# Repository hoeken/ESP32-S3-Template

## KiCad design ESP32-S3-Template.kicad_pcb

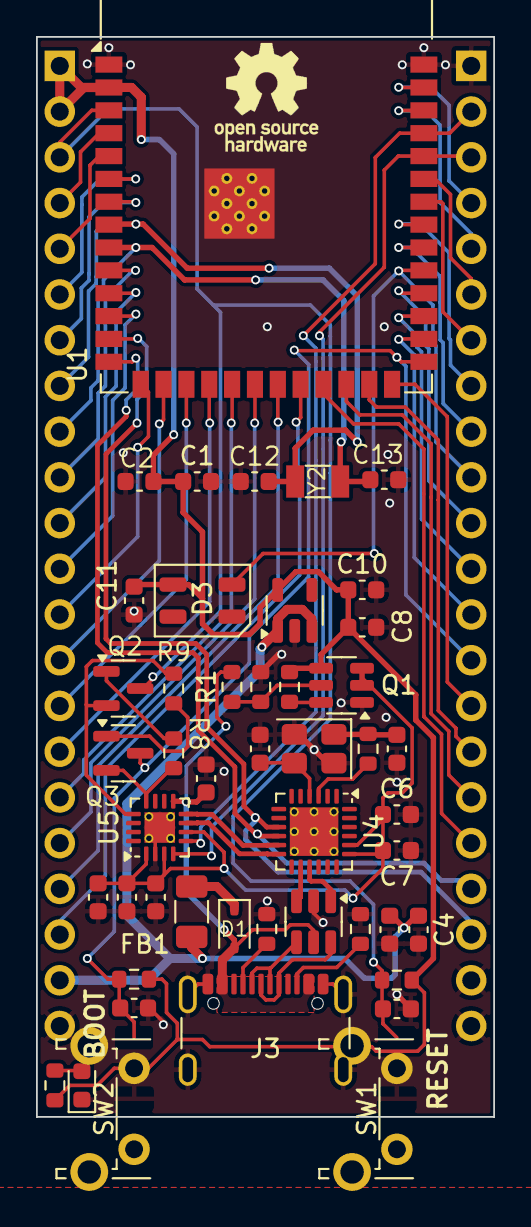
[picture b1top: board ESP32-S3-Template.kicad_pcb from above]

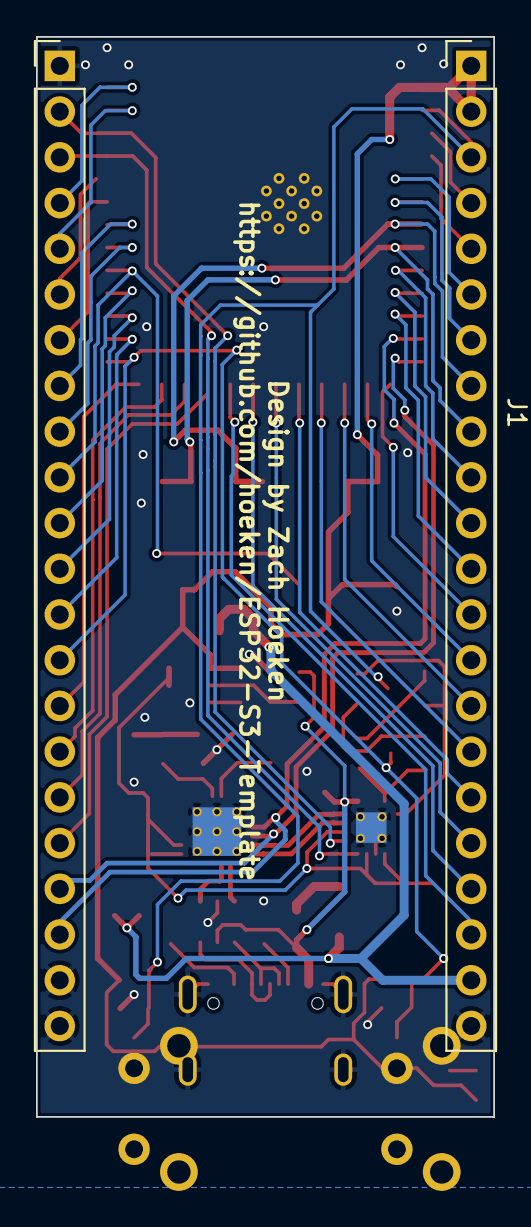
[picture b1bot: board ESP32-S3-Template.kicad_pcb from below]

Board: 4 copper layers, 25.4 x 60.0 mm, 50 parts (2 on the bottom side), 61 nets.

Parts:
C1: 22uF; C_0603_1608Metric
C2, C11, C14, C15, C17: 100nF; C_0603_1608Metric
C3, C10, C16: 10uF; C_0603_1608Metric
C4, C6, C7, C8, C19: 1uF; C_0603_1608Metric
C5, C9, C12, C13: 15pF; C_0603_1608Metric
C18: 4.7uF; C_0603_1608Metric
D1: 1N5819WS; D_SOD-323
D2: RED; LED_0603_1608Metric
D3: WS2812B-Mini; LED_WS2812B-Mini_PLCC4_3.5x3.5mm
FB1: 1.5A; Fuse_1206_3216Metric
J1, J2: Conn_01x22; PinHeader_1x22_P2.54mm_Vertical
J3: USB_TYPE_C_16PIN; USB_C_Receptacle_GCT_USB4105-xx-A_16P_TopMnt_Horizontal
Q1: FDC6330L; TSOT-23-6
Q2, Q3: S8050; SOT-23
R1: 100R; R_0603_1608Metric
R2, R3: 100k; R_0603_1608Metric
R4, R5, R6: 5.1k; R_0603_1608Metric
R7: 1k; R_0603_1608Metric
R8, R9, R10, R11: 10k; R_0603_1608Metric
S1: Logo_Open_Hardware_Small; OSHW-Logo_5.7x6mm_SilkScreen
SW1: RESET; SW_Tactile_SPST_Angled_PTS645Vx58-2LFS
SW2: BOOT; SW_Tactile_SPST_Angled_PTS645Vx58-2LFS
U1: ESP32-S3-WROOM-1-N16R8; ESP32-S3-WROOM-1
U2: USBLC6-2SC6; SOT-23-6
U3: XC6210B332MR; SOT-23-5
U4: CH334F; QFN-24-1EP_4x4mm_P0.5mm_EP2.7x2.7mm_ThermalVias
U5: CH343P; QFN-16-1EP_3x3mm_P0.5mm_EP1.7x1.7mm_ThermalVias
Y1: 12Mhz; Crystal_SMD_SeikoEpson_TSX3225-4Pin_3.2x2.5mm
Y2: 32.768kHz; Crystal_SMD_3215-2Pin_3.2x1.5mm

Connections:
+3.3V: C1.1, C2.1, C8.1, C10.1, C11.1, D2.2 (A), D3.1 (VDD), J1.1, J1.2, Q1.4 (S2), R2.2, R10.1, R11.2, U1.2 (3V3), U3.5 (VOUT)
+5V: C3.1, C4.1, FB1.2, J1.21, U3.1 (VIN), U3.3 (CE)
/ENABLE: C18.1, J1.3, Q2.3 (C), R10.2, SW1.1, U1.3 (EN)
/ESP32-S3/3.3VUSB: C6.1, C7.2, C14.1, C15.1, C17.1, Q1.2 (D2), Q1.3 (D2), U4.19 (V5), U4.20 (V33), U5.1 (VIO), U5.3 (VDD5), U5.6 (V3_{OUT})
/ESP32-S3/CC1_1: J3.A5 (CC1), R4.1
/ESP32-S3/CC2_1: J3.B5 (CC2), R5.1
/ESP32-S3/DTR: Q3.2 (E), R8.1, U5.12 (~DTR)
/ESP32-S3/HUB_D+: U2.1 (I/O1), U4.15 (D+U)
/ESP32-S3/HUB_D-: U2.3 (I/O2), U4.14 (D-U)
/ESP32-S3/RTS: Q2.2 (E), R9.1, U5.13 (~RTS)
/ESP32-S3/UART_D+: U4.12 (D+1), U5.7 (UD+)
/ESP32-S3/UART_D-: U4.11 (D-1), U5.8 (UD-)
/ESP32-S3/USB_D+: J3.A6 (D+), J3.B6 (D+), U2.6 (I/O1)
/ESP32-S3/USB_D-: J3.A7 (D-), J3.B7 (D-), U2.4 (I/O2)
/ESP32-S3/VBUS: C16.2, D1.2 (A), J3.A4 (VBUS), J3.A9 (VBUS), J3.B4 (VBUS), J3.B9 (VBUS), R1.2, U2.5 (VBUS), U5.9 (VBUS)
/ESP_RX0: J2.3, U1.36 (RXD0), U5.4 (TXD)
/ESP_TX0: J2.2, U1.37 (TXD0), U5.5 (RXD)
/ESP_USB+: J2.19, U1.14 (USB_D+), U4.10 (D+2)
/ESP_USB-: J2.20, U1.13 (USB_D-), U4.9 (D-2)
/GPIO0: C19.2, J2.14, Q3.3 (C), R11.1, SW2.1, U1.27 (IO0)
/GPIO1: J2.4, U1.39 (IO1)
/GPIO2: J2.5, U1.38 (IO2)
/GPIO3: J1.13, U1.15 (IO3)
/GPIO4: J1.4, U1.4 (IO4)
/GPIO5: J1.5, U1.5 (IO5)
/GPIO6: J1.6, U1.6 (IO6)
/GPIO7: J1.7, U1.7 (IO7)
/GPIO8: J1.12, U1.12 (IO8)
/GPIO9: J1.15, U1.17 (IO9)
/GPIO10: J1.16, U1.18 (IO10)
/GPIO11: J1.17, U1.19 (IO11)
/GPIO12: J1.18, U1.20 (IO12)
/GPIO13: J1.19, U1.21 (IO13)
/GPIO14: J1.20, U1.22 (IO14)
/GPIO15: C12.2, J1.8, U1.8 (IO15), Y2.2
/GPIO16: C13.1, J1.9, U1.9 (IO16), Y2.1
/GPIO17: J1.10, U1.10 (IO17)
/GPIO18: J1.11, U1.11 (IO18)
/GPIO21: J2.18, U1.23 (IO21)
/GPIO35: J2.13, U1.28 (IO35)
/GPIO36: J2.12, U1.29 (IO36)
/GPIO37: J2.11, U1.30 (IO37)
/GPIO38: D3.4 (DIN), J2.10, U1.31 (IO38)
/GPIO39: J2.9, U1.32 (IO39)
/GPIO40: J2.8, U1.33 (IO40)
/GPIO41: J2.7, U1.34 (IO41)
/GPIO42: J2.6, U1.35 (IO42)
/GPIO45: J2.15, U1.26 (IO45)
/GPIO46: J1.14, U1.16 (IO46)
/GPIO47: J2.17, U1.24 (IO47)
/GPIO48: J2.16, U1.25 (IO48)
GND: C1.2, C2.2, C3.2, C4.2, C5.2, C6.2, C7.1, C8.2, C9.2, C10.2, C11.2, C12.1, C13.2, C14.2, C15.2, C16.1, C17.2, C18.2, C19.1, D3.3 (VSS), J1.22, J2.1, J2.21, J2.22, J3.A1 (GND), J3.A12 (GND), J3.B1 (GND), J3.B12 (GND), J3.S1 (SHIELD), Q1.1 (S1), R3.1, R4.2, R5.2, R6.2, SW1.2, SW2.2, U1.1 (GND), U1.40 (GND), U1.41 (GND), U2.2 (GND), U3.2 (GND), U4.25 (GND), U5.2 (GND), U5.17 (GND_EPAD), Y1.2, Y1.4
unnamed: C9.1, R7.1, Y1.1
unnamed: D1.1 (K), FB1.1
unnamed: D2.1 (K), R6.1
unnamed: Q1.6 (D1), R2.1
unnamed: Q1.5 (G1), R1.1, R3.2
unnamed: Q2.1 (B), R8.2
unnamed: Q3.1 (B), R9.2
unnamed: C5.1, U4.4 (XIN), Y1.3
unnamed: R7.2, U4.3 (XOUT)

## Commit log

2025-08-20 initial group of modifications.
2025-08-21 board is fully routed.
2025-08-22 fully routed, erc+drc pass, 3d models
2025-08-22 silkscreen
2025-08-22 a little bit of a reorg
2025-08-22 checking bom
2025-08-23 reworked the esp module symbol with more pin info.
2025-08-28 i think its ready for reddit.
2025-08-29 another full pass over the schematic and layout
2025-09-07 Rev A sent to JLC for production
2025-10-02 pulled in brineomatic version
